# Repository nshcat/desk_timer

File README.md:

# desk_timer

# TODOs

[ ] For some reason, I needed to add "-isystem /usr/arm-none-eabi/include/c++/14.2.0" to the `compile_commands.json` entry for `main.cxx` in order for `clangd` to find the system includes.

[ ] Compiling and linking u8g2 as a static library does not seem to work - the final `desk_timer.elf` binary is way too large (multiple megabytes big), and while having LTO enabled via the CMake LTO settings shrinks the binary again, it doesnt work on the MCU. I did have to use `-ffunction-sections` and `-fdata-sections`, maybe that messed up the final `.bin` flash image generation, because it creates individual sections for each function and data symbol?

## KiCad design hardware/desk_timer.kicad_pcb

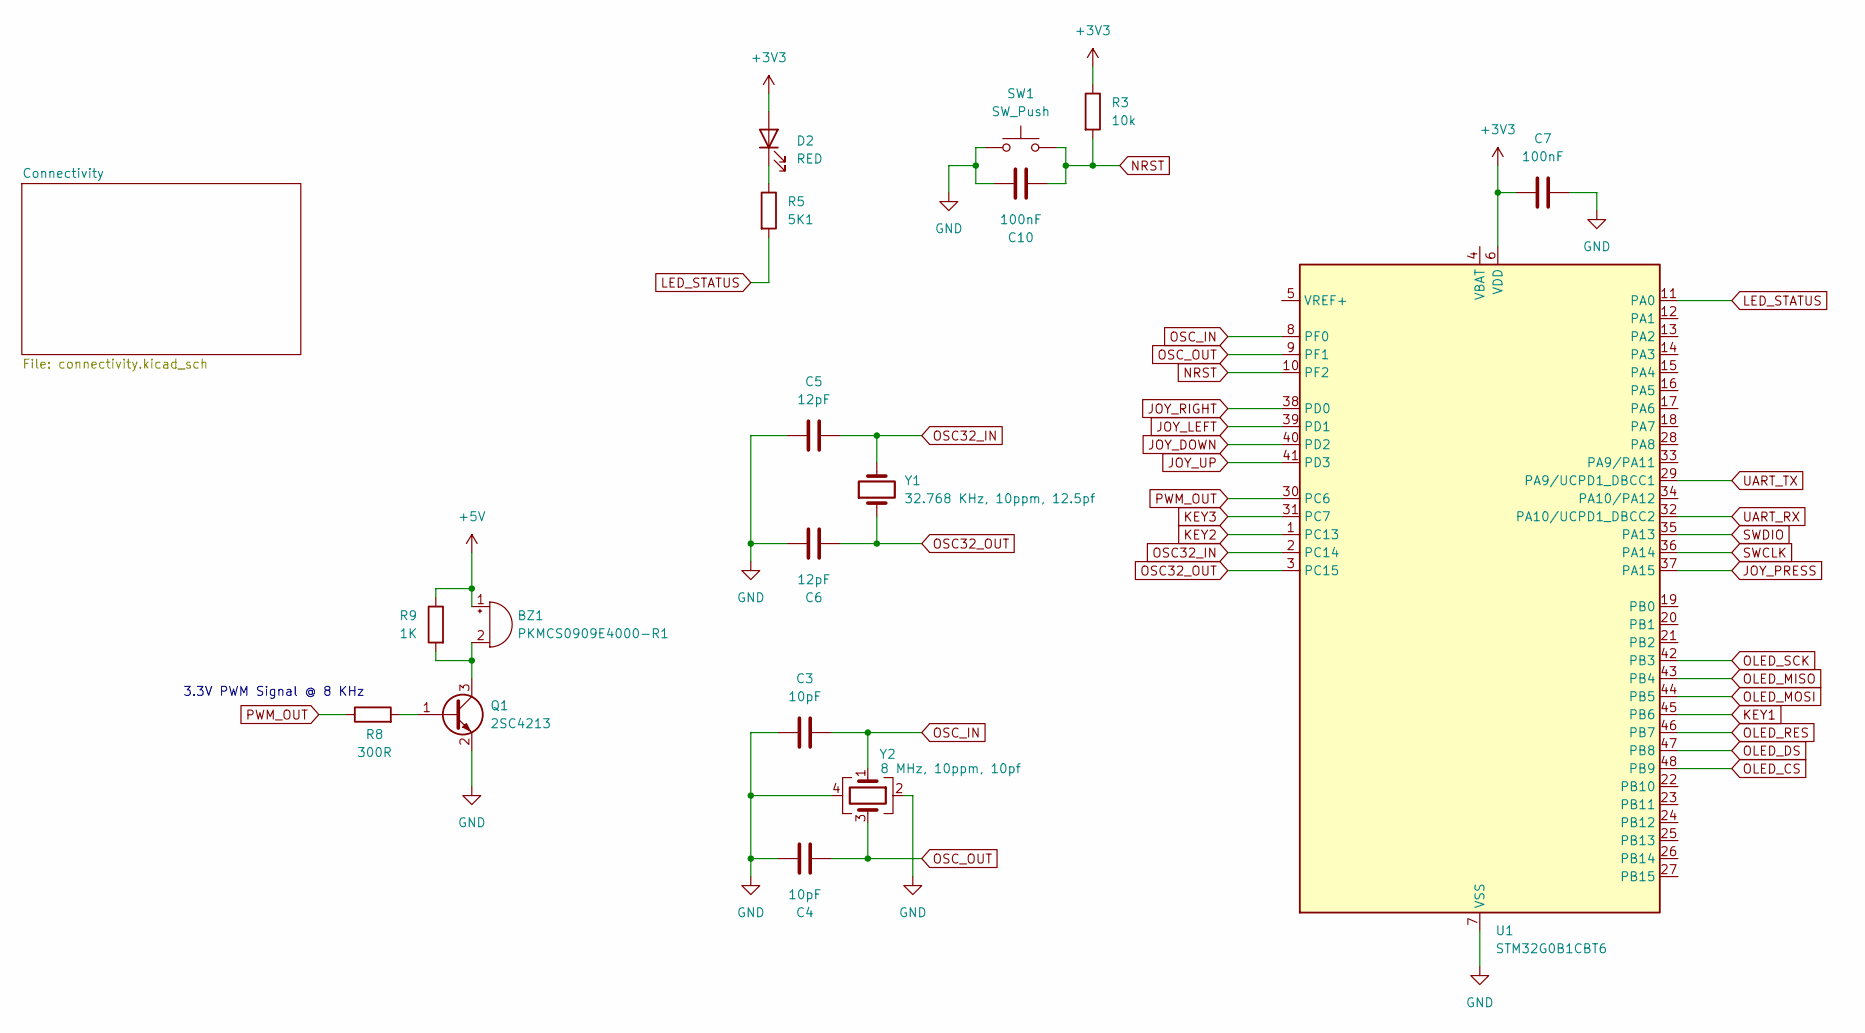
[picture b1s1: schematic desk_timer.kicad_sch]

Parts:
BZ1: PKMCS0909E4000-R1; Buzzer_Murata_PKMCS0909E; LCSC Part # C910763
C3, C4: 10pF; C_0402_1005Metric; LCSC Part # C32949
C5, C6: 12pF; C_0402_1005Metric; LCSC Part # C1547
C7, C10: 100nF; C_0805_2012Metric; LCSC Part # C28233
D2: RED; LED_0402_1005Metric; LCSC Part # C130719
Q1: 2SC4213; SOT-323_SC-70; LCSC Part # C516169
R3: 10k; R_0402_1005Metric; LCSC Part # C25744
R5: 5K1; R_0402_1005Metric; LCSC Part # C25905
R8: 300R; R_1206_3216Metric_Pad1.30x1.75mm_HandSolder; LCSC Part # C17887
R9: 1K; R_0402_1005Metric; LCSC Part # C11702
SW1: SW_Push; SW_SPST_B3U-1000P; LCSC Part # C231329
U1: STM32G0B1CBT6; LQFP-48_7x7mm_P0.5mm; LCSC Part # C2847904
Y1: 32.768 KHz, 10ppm, 12.5pf; Crystal_SMD_3215-2Pin_3.2x1.5mm; LCSC Part # C32346
Y2: 8 MHz, 10ppm, 10pf; Crystal_SMD_3225-4Pin_3.2x2.5mm; LCSC Part # C400090

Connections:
+3V3: C7.1, D2.2 (A), R3.1, U1.6 (VDD); also elsewhere on the board
+5V: BZ1.1 (+), R9.1; also elsewhere on the board
GND: C3.2, C4.2, C5.1, C6.2, C7.2, C10.1, Q1.2 (E), SW1.1, U1.7 (VSS), Y2.2, Y2.4; also elsewhere on the board
JOY_DOWN: U1.40 (PD2); also elsewhere on the board
JOY_LEFT: U1.39 (PD1); also elsewhere on the board
JOY_PRESS: U1.37 (PA15); also elsewhere on the board
JOY_RIGHT: U1.38 (PD0); also elsewhere on the board
JOY_UP: U1.41 (PD3); also elsewhere on the board
KEY1: U1.45 (PB6); also elsewhere on the board
KEY2: U1.1 (PC13); also elsewhere on the board
KEY3: U1.31 (PC7); also elsewhere on the board
LED_STATUS: R5.2, U1.11 (PA0)
NRST: C10.2, R3.2, SW1.2, U1.10 (PF2); also elsewhere on the board
unnamed: BZ1.2 (-), Q1.3 (C), R9.2
unnamed: D2.1 (K), R5.1
unnamed: Q1.1 (B), R8.2
OLED_CS: U1.48 (PB9); also elsewhere on the board
OLED_DS: U1.47 (PB8); also elsewhere on the board
OLED_MISO: U1.43 (PB4); also elsewhere on the board
OLED_MOSI: U1.44 (PB5); also elsewhere on the board
OLED_RES: U1.46 (PB7); also elsewhere on the board
OLED_SCK: U1.42 (PB3); also elsewhere on the board
OSC32_IN: C5.2, U1.2 (PC14), Y1.2
OSC32_OUT: C6.1, U1.3 (PC15), Y1.1
OSC_IN: C3.1, U1.8 (PF0), Y2.1
OSC_OUT: C4.1, U1.9 (PF1), Y2.3
PWM_OUT: R8.1, U1.30 (PC6)
SWCLK: U1.36 (PA14); also elsewhere on the board
SWDIO: U1.35 (PA13); also elsewhere on the board
UART_RX: U1.32 (PA10/UCPD1_DBCC2); also elsewhere on the board
UART_TX: U1.29 (PA9/UCPD1_DBCC1); also elsewhere on the board

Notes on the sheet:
3.3V PWM Signal @ 8 KHz

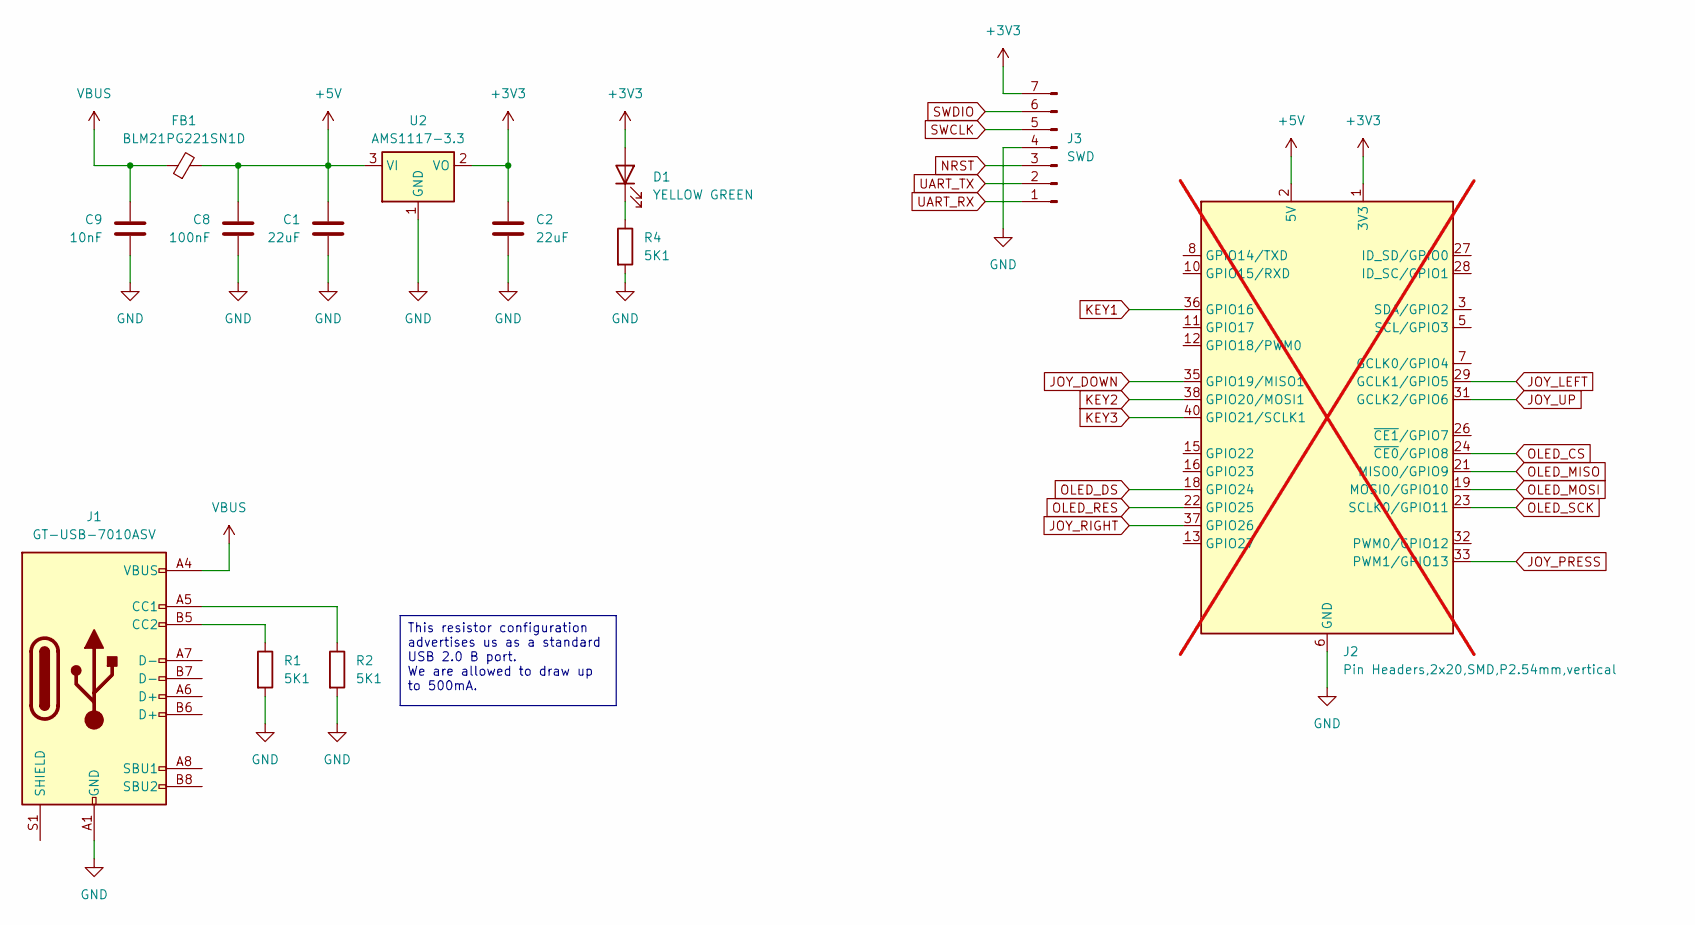
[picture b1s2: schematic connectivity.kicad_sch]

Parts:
C1, C2: 22uF; C_1206_3216Metric; LCSC Part # C12891
C8: 100nF; C_0805_2012Metric; LCSC Part # C28233
C9: 10nF; C_0805_2012Metric; LCSC Part # C18741
D1: YELLOW GREEN; LED_0402_1005Metric; LCSC Part # C130722
FB1: BLM21PG221SN1D; L_0805_2012Metric; LCSC Part # C85840
J1: GT-USB-7010ASV; USB_C_Receptacle_G-Switch_GT-USB-7010ASV; LCSC Part # C2988369
J2: Pin Headers,2x20,SMD,P2.54mm,vertical; PinHeader_2x20_P2.54mm_Vertical; not fitted
J3: SWD; PinHeader_1x07_P2.54mm_Horizontal
R1, R2, R4: 5K1; R_0402_1005Metric; LCSC Part # C25905
U2: AMS1117-3.3; SOT-223-3_TabPin2; LCSC Part # C6186

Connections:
+3V3: C2.1, D1.2 (A), J2.1 (3V3), J2.17 (3V3), J3.7, U2.2 (VO); also elsewhere on the board
+5V: C1.1, C8.2, FB1.2, J2.2 (5V), J2.4 (5V), U2.3 (VI); also elsewhere on the board
GND: C1.2, C2.2, C8.1, C9.1, J1.A1 (GND), J1.A12 (GND), J1.B1 (GND), J1.B12 (GND), J2.6 (GND), J2.9 (GND), J2.14 (GND), J2.20 (GND), J2.25 (GND), J2.30 (GND), J2.34 (GND), J2.39 (GND), J3.4, R1.2, R2.2, R4.2, U2.1 (GND); also elsewhere on the board
JOY_DOWN: J2.35 (GPIO19/MISO1); also elsewhere on the board
JOY_LEFT: J2.29 (GCLK1/GPIO5); also elsewhere on the board
JOY_PRESS: J2.33 (PWM1/GPIO13); also elsewhere on the board
JOY_RIGHT: J2.37 (GPIO26); also elsewhere on the board
JOY_UP: J2.31 (GCLK2/GPIO6); also elsewhere on the board
KEY1: J2.36 (GPIO16); also elsewhere on the board
KEY2: J2.38 (GPIO20/MOSI1); also elsewhere on the board
KEY3: J2.40 (GPIO21/SCLK1); also elsewhere on the board
NRST: J3.3; also elsewhere on the board
unnamed: D1.1 (K), R4.1
unnamed: J1.A5 (CC1), R2.1
unnamed: J1.B5 (CC2), R1.1
OLED_CS: J2.24 (~CE0/GPIO8); also elsewhere on the board
OLED_DS: J2.18 (GPIO24); also elsewhere on the board
OLED_MISO: J2.21 (MISO0/GPIO9); also elsewhere on the board
OLED_MOSI: J2.19 (MOSI0/GPIO10); also elsewhere on the board
OLED_RES: J2.22 (GPIO25); also elsewhere on the board
OLED_SCK: J2.23 (SCLK0/GPIO11); also elsewhere on the board
SWCLK: J3.5; also elsewhere on the board
SWDIO: J3.6; also elsewhere on the board
UART_RX: J3.1; also elsewhere on the board
UART_TX: J3.2; also elsewhere on the board
VBUS: C9.2, FB1.1, J1.A4 (VBUS), J1.A9 (VBUS), J1.B4 (VBUS), J1.B9 (VBUS)

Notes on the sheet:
This resistor configuration advertises us as a standard USB 2.0 B port. We are allowed to draw up to 500mA.

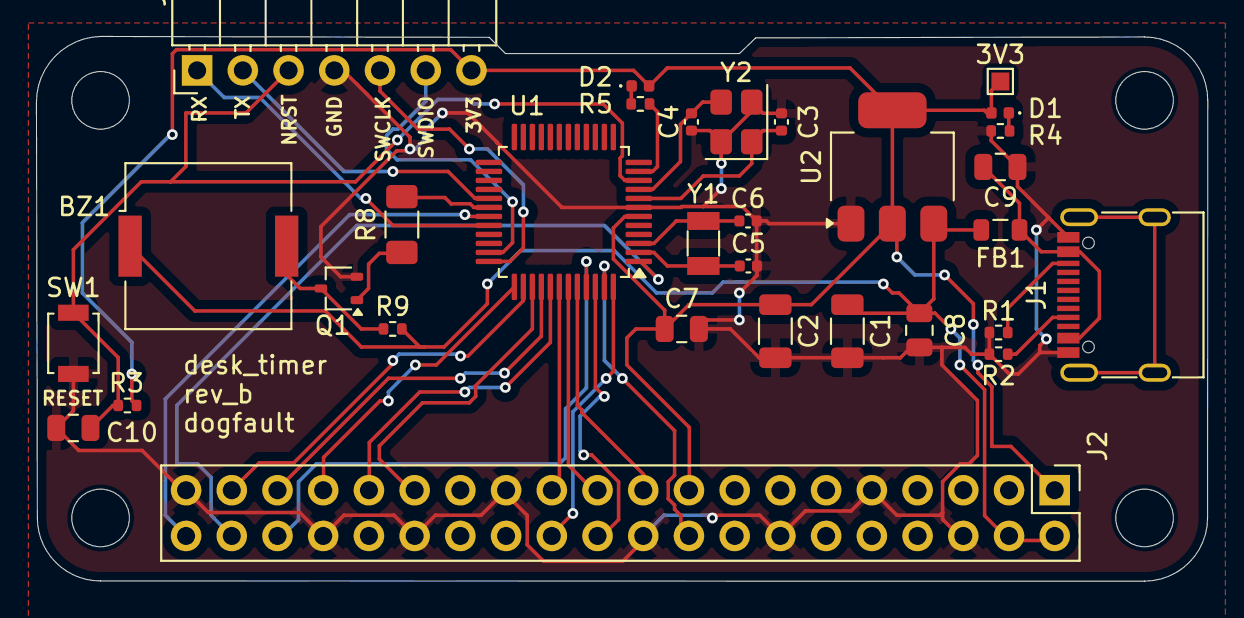
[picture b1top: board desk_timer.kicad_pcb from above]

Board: 2 copper layers, 65.1 x 30.3 mm, 31 parts (0 on the bottom side), 35 nets.

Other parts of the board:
3V3: TestPoint_Pad_1.0x1.0mm

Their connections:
+3V3: 3V3.1; also elsewhere on the board

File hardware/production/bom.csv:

Designator,Footprint,Quantity,Value,LCSC Part #
BZ1,Buzzer_Murata_PKMCS0909E,1,PKMCS0909E4000-R1,C910763
"C1, C2",1206,2,22uF,C12891
"C10, C7, C8",0805,3,100nF,C28233
"C3, C4",0402,2,10pF,C32949
"C5, C6",0402,2,12pF,C1547
C9,0805,1,10nF,C18741
D1,0402,1,YELLOW GREEN,C130722
D2,0402,1,RED,C130719
D3,D_SOD-523,1,1N4148WT,C7420320
FB1,0805,1,BLM21PG221SN1D,C85840
J1,USB_C_Receptacle_G-Switch_GT-USB-7010ASV,1,GT-USB-7010ASV,C2988369
Q1,SOT-323_SC-70,1,2SC4213,C516169
"R1, R2, R4, R5",0402,4,5K1,C25905
"R3, R6",0402,2,10k,C25744
R7,0402,1,280R,C2929998
SW1,SW_SPST_B3U-1000P,1,SW_Push,C231329
U1,LQFP-48_7x7mm_P0.5mm,1,STM32G0B1CBT6,C2847904
U2,SOT-223-3_TabPin2,1,AMS1117-3.3,C6186
Y1,Crystal_SMD_3215-2Pin_3.2x1.5mm,1,"32.768 KHz, 10ppm, 12.5pf",C32346
Y2,Crystal_SMD_3225-4Pin_3.2x2.5mm,1,"8 MHz, 10ppm, 10pf",  C400090

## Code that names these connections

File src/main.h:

/* USER CODE BEGIN Header */
/**
  ******************************************************************************
  * @file           : main.h
  * @brief          : Header for main.c file.
  *                   This file contains the common defines of the application.
  ******************************************************************************
  * @attention
  *
  * Copyright (c) 2025 STMicroelectronics.
  * All rights reserved.
  *
  * This software is licensed under terms that can be found in the LICENSE file
  * in the root directory of this software component.
  * If no LICENSE file comes with this software, it is provided AS-IS.
  *
  ******************************************************************************
  */
/* USER CODE END Header */

/* Define to prevent recursive inclusion -------------------------------------*/
#ifndef __MAIN_H
#define __MAIN_H

#ifdef __cplusplus
extern "C" {
#endif

/* Includes ------------------------------------------------------------------*/
#include "stm32g0xx_hal.h"

/* Private includes ----------------------------------------------------------*/
/* USER CODE BEGIN Includes */

/* USER CODE END Includes */

/* Exported types ------------------------------------------------------------*/
/* USER CODE BEGIN ET */

/* USER CODE END ET */

/* Exported constants --------------------------------------------------------*/
/* USER CODE BEGIN EC */

/* USER CODE END EC */

/* Exported macro ------------------------------------------------------------*/
/* USER CODE BEGIN EM */

/* USER CODE END EM */

void HAL_TIM_MspPostInit(TIM_HandleTypeDef *htim);

/* Exported functions prototypes ---------------------------------------------*/
void Error_Handler(void);

/* USER CODE BEGIN EFP */

/* USER CODE END EFP */

/* Private defines -----------------------------------------------------------*/
#define KEY_2_Pin GPIO_PIN_13
#define KEY_2_GPIO_Port GPIOC
#define KEY_2_EXTI_IRQn EXTI4_15_IRQn
#define LED_STATUS_Pin GPIO_PIN_0
#define LED_STATUS_GPIO_Port GPIOA
#define LED_STATUS2_Pin GPIO_PIN_6
#define LED_STATUS2_GPIO_Port GPIOC
#define KEY_3_Pin GPIO_PIN_7
#define KEY_3_GPIO_Port GPIOC
#define KEY_3_EXTI_IRQn EXTI4_15_IRQn
#define JOY_PRESS_Pin GPIO_PIN_15
#define JOY_PRESS_GPIO_Port GPIOA
#define JOY_PRESS_EXTI_IRQn EXTI4_15_IRQn
#define JOY_RIGHT_Pin GPIO_PIN_0
#define JOY_RIGHT_GPIO_Port GPIOD
#define JOY_RIGHT_EXTI_IRQn EXTI0_1_IRQn
#define JOY_LEFT_Pin GPIO_PIN_1
#define JOY_LEFT_GPIO_Port GPIOD
#define JOY_LEFT_EXTI_IRQn EXTI0_1_IRQn
#define JOY_DOWN_Pin GPIO_PIN_2
#define JOY_DOWN_GPIO_Port GPIOD
#define JOY_DOWN_EXTI_IRQn EXTI2_3_IRQn
#define JOY_UP_Pin GPIO_PIN_3
#define JOY_UP_GPIO_Port GPIOD
#define JOY_UP_EXTI_IRQn EXTI2_3_IRQn
#define OLED_SCK_Pin GPIO_PIN_3
#define OLED_SCK_GPIO_Port GPIOB
#define OLED_MISO_Pin GPIO_PIN_4
#define OLED_MISO_GPIO_Port GPIOB
#define OLED_MOSI_Pin GPIO_PIN_5
#define OLED_MOSI_GPIO_Port GPIOB
#define KEY_1_Pin GPIO_PIN_6
#define KEY_1_GPIO_Port GPIOB
#define KEY_1_EXTI_IRQn EXTI4_15_IRQn
#define OLED_RES_Pin GPIO_PIN_7
#define OLED_RES_GPIO_Port GPIOB
#define OLED_DS_Pin GPIO_PIN_8
#define OLED_DS_GPIO_Port GPIOB
#define OLED_CS_Pin GPIO_PIN_9
#define OLED_CS_GPIO_Port GPIOB

/* USER CODE BEGIN Private defines */

/* USER CODE END Private defines */

#ifdef __cplusplus
}
#endif

#endif /* __MAIN_H */

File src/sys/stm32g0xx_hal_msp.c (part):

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
    __HAL_RCC_GPIOB_CLK_ENABLE();
    /**SPI3 GPIO Configuration
    PB3     ------> SPI3_SCK
    PB4     ------> SPI3_MISO
    PB5     ------> SPI3_MOSI
    */
    GPIO_InitStruct.Pin = OLED_SCK_Pin|OLED_MISO_Pin|OLED_MOSI_Pin;
    GPIO_InitStruct.Mode = GPIO_MODE_AF_PP;
    GPIO_InitStruct.Pull = GPIO_NOPULL;
    GPIO_InitStruct.Speed = GPIO_SPEED_FREQ_LOW;
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    __HAL_RCC_SPI3_CLK_DISABLE();

    /**SPI3 GPIO Configuration
    PB3     ------> SPI3_SCK
    PB4     ------> SPI3_MISO
    PB5     ------> SPI3_MOSI
    */
    HAL_GPIO_DeInit(GPIOB, OLED_SCK_Pin|OLED_MISO_Pin|OLED_MOSI_Pin);

    /* USER CODE BEGIN SPI3_MspDeInit 1 */

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
    __HAL_RCC_GPIOC_CLK_ENABLE();
    /**TIM2 GPIO Configuration
    PC6     ------> TIM2_CH3
    */
    GPIO_InitStruct.Pin = GPIO_PIN_6;
    GPIO_InitStruct.Mode = GPIO_MODE_AF_PP;
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
    __HAL_RCC_GPIOA_CLK_ENABLE();
    /**USART1 GPIO Configuration
    PA9     ------> USART1_TX
    PA10     ------> USART1_RX
    */
    GPIO_InitStruct.Pin = GPIO_PIN_9|GPIO_PIN_10;
    GPIO_InitStruct.Mode = GPIO_MODE_AF_PP;
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    __HAL_RCC_USART1_CLK_DISABLE();

    /**USART1 GPIO Configuration
    PA9     ------> USART1_TX
    PA10     ------> USART1_RX
    */
    HAL_GPIO_DeInit(GPIOA, GPIO_PIN_9|GPIO_PIN_10);

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
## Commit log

2025-06-19 Add stm32 cmake project files
2025-06-19 Added gitignore
2025-06-19 Source, debugging helpers etc
2025-06-24 Added kicad project
2025-06-25 Switched to STM32G0B1, improved usage reporting, etc
2025-06-30 Added flash target
2025-07-02 Finished board
2025-07-08 More changes
2025-07-14 Fixed display SPI. It was clocking too fast for the SH1106 controller
2025-08-03 Reorganized repo
2025-08-03 Fixed code not working on MCU
2025-08-03 Edited readme
